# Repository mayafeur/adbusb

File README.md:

**Arduino software to share an ADB keyboard between an ADB computer (old Macintosh and Apple IIgs) and a USB computer.**

## What works

- adb passthrough between a macintosh and a keyboard
  - handle other devices on the bus (like a mouse)
  - relay softpower signal (macintosh ii, quadra, powermac...)
  - no electric connection between data lines or softpower lines
- adb keyboard to usb-hid conversion:
  - iso and ansi layouts
  - locking caps lock
  - power key in usb (translated as 0x66 "keyboard power")
- auto switch when a computer is off
- tested on multiple keyboards: aek ii, m0116/m0118, appledesign
- tested on macintosh se and powermac g3

## What don't work yet

- keyboard leds on usb: the *keyboard.h* library doesn't handle hid output reports
- hotplugging adb: works randomly, the microcontroller don't like that
- mouse passthrough in usb mode
- keyboard detection at startup by the macintosh if arduino in usb mode: still usable tho
- collision detection handling: the program calls the keyboard at address 2

## Hardware needed

- arduino pro micro because it works on 5V and is hid capable
- 2 mini-din 4 pin connectors (only one if using only adb-to-usb)
- a resistor (1K) for the pull up
- a button (optional if using only adb-to-usb)
- a diode (optional, to power the arduino from adb)

## How to build it

- connect button between 2 and GND
- connect 9 to the mini-din A pin 1 (computer adb data)
- connect 8 to the mini-din A pin 2 (computer adb softpower)
- connect mini-din A pin 3 to RAW through the diode (pass from mini-DIN to RAW)
- connect 10 to the mini-din B pin 1 (keyboard adb data) then to VCC through resistor
- connect 16 to the mini-din B pin 2 (keyboard adb softpower)
- connect RAW to the mini-din B pin 3 (keyboard 5V power)
- connect GND on the two mini-din pins 4
- mark din A as the macintosh connector and din B as the keyboard connector (put a sticker or whatever)

Mini-DIN female connector front view :
```
/------\
| 4  3 |
| 2  1 |
\__==__/
```

Arduino Pro Micro pinout :
```
                                ___________ 
                     PD3  TXD  |    USB    |  RAW        --- keyboard pin 3 ---
                     PD2   20  |           |  GND        --- keyboard pin 4    |
computer pin 4 ---        GND  |           |  RST                              |
  button pin 1 ---        GND  |           |  VCC                              |
  button pin 2 ---   PD1    2  |           |  A3   PF4                         |
                     PD0    3  |           |  A2   PF5                         _
                     PD4    4  |           |  A1   PF6                        | |
                     PC6    5  |           |  A0   PF7            1K resistor | |
                     PD7    6  |           |  15   PB1                        |_|
                     PE6    7  |           |  14   PB3                         |
computer pin 2 ---   PB4    8  |           |  16   PB2   --- keyboard pin 2    |
computer pin 1 ---   PB5    9  |___________|  10   PB6   --- keyboard pin 1 ---
computer pin 3 --->| RAW
```

## How to compile and upload it

1. install `arduino-cli`
2. `arduino-cli core install arduino:avr`
3. `arduino-cli lib install Keyboard`
4. compile this project by `cd` in then `arduino-cli compile --fqbn arduino:avr:micro`
5. connect the board to the computer
6. get board port with `arduino-cli board list`
7. upload it `arduino-cli upload -p /dev/.......`

## References

- [Guide to the Macintosh family hardware, Chapter 8 : Apple Desktop Bus, Apple, 1990](https://archive.org/details/apple-guide-macintosh-family-hardware/page/n325/mode/2up)
- [Apple Desktop Bus Protocol, lopaciuk.eu, 2021](https://www.lopaciuk.eu/2021/03/26/apple-adb-protocol.html)
- [Understanding the ADB Service Request Signal, bigmessowires, 2016](https://www.bigmessowires.com/2016/03/30/understanding-the-adb-service-request-signal/)
- [Apple Desktop Bus (ADB), wiki.preterhuman.net](https://wiki.preterhuman.net/Apple_Desktop_Bus_(ADB))

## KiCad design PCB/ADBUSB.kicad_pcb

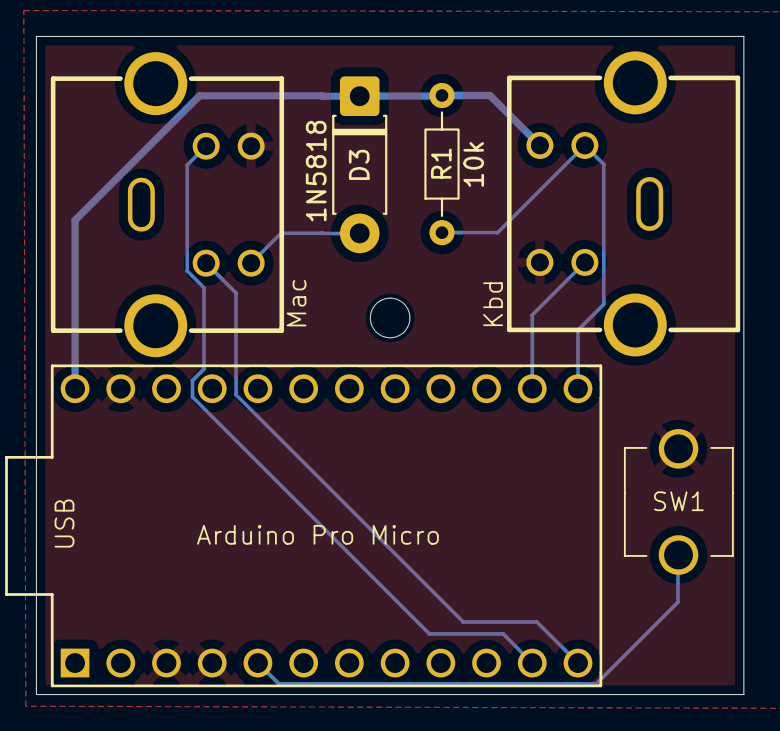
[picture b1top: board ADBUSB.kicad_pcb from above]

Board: 2 copper layers, 39.3 x 36.6 mm, 6 parts (0 on the bottom side), 8 nets.

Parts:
D3: 1N5818; D_DO-41_SOD81_P7.62mm_Horizontal
J1, J2: MLD-MDC-4-02
R1: 10k; R_Axial_DIN0204_L3.6mm_D1.6mm_P7.62mm_Horizontal
SW1: SW_SPST; SPST_power_switch_horizontal
U1: ProMicro

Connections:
GND: J1.4, J2.4, SW1.2, U1.3 (GND), U1.4 (GND), U1.23 (GND)
unnamed: D3.2 (A), J1.3
unnamed: J2.2, U1.14 (B2)
unnamed: J1.2, U1.11 (B4)
unnamed: J1.1, U1.12 (B5)
unnamed: J2.1, R1.1, U1.13 (B6)
unnamed: SW1.1, U1.5 (SDA)
RAW_5V: D3.1 (K), J2.3, R1.2, U1.24 (RAW)

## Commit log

2026-06-21 illustration
2026-06-22 add mouse support through adb
2026-06-22 add softpower
2026-06-24 breaking changes
    refactoring
    button at different pin
    different button handling
2026-06-24 detection for unplugged device
2026-06-24 Update for diode, pushbutton, raw
2026-06-24 fix bascule off
2026-06-25 new readme :)
